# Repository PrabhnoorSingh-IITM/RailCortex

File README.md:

# 🚄 RailCortex

<p align="center">
  <a href="https://drive.google.com/file/d/1XESk1WhmcyDZzcQoyr-ekqZNMPGzPJtn/view?usp=sharing"><strong>Watch Demo Video</strong></a> | 
  <a href="https://drive.google.com/file/d/1N0aOrDR9K62Z9wJUEEKm0sZDDuzc8ooX/view?usp=sharing"><strong>View Pitch Deck (PPT)</strong></a>
</p>

RailCortex is an autonomous, dual-mode Cyber-Physical System (CPS) engineered to modernize transit operations. It replaces passive tracking with an active cognitive network, bridging the gap between **deterministic mathematical optimization**, **custom physical hardware**, and **Agentic AI**.

In its primary state, RailCortex operates as a **Level 4 Digital Twin**. Powered by a high-performance WebGL rendering engine, it visualizes spatial datasets at 60fps. Rather than relying on human dispatchers to resolve platform conflicts, the system ingests live edge telemetry and utilizes **Mixed-Integer Linear Programming (MILP)** via PuLP to deterministically reroute trains, absorbing localized delays before they cascade across the grid.

When a physical disaster strikes, RailCortex’s custom-engineered IoT edge node—equipped with an MPU6050 accelerometer, NEO-6M GPS, and environmental sensors—detects the kinetic anomaly and instantly overrides the network. The system transitions into **Emergency Response Mode**, deploying a rigid, deterministic **LangGraph Multi-Agent Swarm**.

---

## 🧭 Dual-Mode Capabilities

### 1. Normal Operations: The Digital Twin
A high-performance WebGL spatial dashboard that functions as a Level 4 digital twin of the physical railway infrastructure.
*   **Live Telemetry Ingestion:** Continuously tracks real-time train movement, velocity, and track congestion parameters via WebSockets.
*   **Mathematical Rerouting:** Utilizes Mixed-Integer Linear Programming (MILP) to autonomously calculate platform reallocations and prevent network gridlock during extreme weather anomalies or track blockages.
*   **GPU-Accelerated Rendering:** Leverages `deck.gl` to render massive spatial datasets (dynamic agents, stations, meteorological overlays) at 60fps without browser latency.

### 2. Emergency Response: The Multi-Agent Swarm
Upon detection of a catastrophic event (e.g., derailment) via the custom IoT hardware edge node, the system interrupts standard optimization protocols and deploys an autonomous LangGraph agent swarm.
*   **Zero-Latency Orchestration:** Agents autonomously calculate incident severity based on raw G-force telemetry.
*   **Spatial Discovery:** Executes Overpass QL to programmatically query OpenStreetMap (OSM) for the precise GPS bounding boxes of adjacent medical infrastructure.
*   **Heavy-Vehicle CAD Routing:** Interfaces with Mappls/Google Routes REST APIs to dispatch emergency medical services utilizing traffic-aware, heavy-vehicle optimal trajectories.

---

## 🛠️ Technology Stack
This project strictly avoids simplistic API wrapper methodologies, demonstrating comprehensive engineering execution across hardware, frontend visualization, and algorithmic routing.

### Frontend (Visualization & Interactivity)
*   **Frameworks:** React.js (Vite) + Tailwind CSS + Framer Motion.
*   **Geospatial:** `deck.gl` (WebGL2 / WebGPU spatial rendering framework) + `react-map-gl` (Mapbox GL JS base maps).
*   **State Management:** Zustand (for reactive, global dashboard state).
*   **Animations:** Anime.js (for SVG architecture flows) + Framer Motion (for spring-physics layout reveals).

### Backend (Cognitive & Routing Engine)
*   **Core:** Python 3.11 + FastAPI + WebSockets (for continuous bidirectional telemetry streaming).
*   **Mathematical Optimization:** PuLP (Python-based MILP solver for deterministic routing).
*   **Agentic Framework:** LangGraph + LangChain (Strict state-machine agent orchestration).
*   **LLMs:** OpenAI GPT-4o / GPT-4o-mini (for unstructured parsing and heuristic judgment).

### Hardware Edge Node (IoT)
*   **Microcontroller:** ESP32-WROOM-32.
*   **Sensors:** MPU6050 (Accelerometer/Gyroscope) + NEO-6M (GPS) + BME280 (Meteorological Sensor) + VL53L0X (LiDAR/Time-of-Flight).
*   **Hardware Engineering:** Custom schematics and Gerber files designed in KiCad 8.0.
*   **CAD Enclosure:** 3D-printed housing parametrically modeled in Autodesk Fusion 360.
*(Note: Hardware schematics, Gerber files, and CAD deliverables are located in the `/Hardware` directory).*

---

## 📐 Engineering Principles and Deterministic Architecture
RailCortex was engineered utilizing deterministic mathematics to ensure the safe management of physical infrastructure:
*   **Deterministic Optimization Constraints:** Train platform reallocation and collision avoidance are managed by strict Linear Algebra equations and bounds, explicitly preventing stochastic LLMs from hallucinating physical routes.
*   **Graph-Based Agent State Management:** LangGraph was selected over standard conversational frameworks (e.g., AutoGen, CrewAI) to enforce a rigid, deterministic execution loop during critical emergencies, mathematically guaranteeing fallback protocols if an external API fails.
*   **Hardware-in-the-Loop Integration:** Physical severity and infrastructure degradation models (Kinetic Energy & Weibull Degradation) are calculated directly from physical IoT sensor payloads, eliminating reliance on simulated mock data for critical triggers.

---

## ⚙️ Local Setup Instructions

### 1. Repository Configuration
Clone the repository and enter the directory:
```bash
git clone https://github.com/PrabhnoorSingh-IITM/RailCortex.git
cd RailCortex
```

### 2. Backend Configuration (FastAPI)
```bash
cd backend
python3 -m venv venv
source venv/bin/activate  # On Windows use: venv\Scripts\activate
pip install -r requirements.txt
```

Create a `.env` file within the `/backend` directory:
```env
OPENAI_API_KEY=your_openai_key
MAPPLS_API_KEY=your_routing_key
MAPBOX_ACCESS_TOKEN=your_mapbox_key
```

Initialize the ASGI server:
```bash
uvicorn app.main:app --reload --port 8000
```

### 3. Frontend Configuration (React/Vite)
In a new terminal window:
```bash
cd frontend
npm install
npm run dev
```
Navigate to `http://localhost:5173` to access the Digital Twin interface.

### 4. Hardware Node Deployment 
Navigate to `/Hardware/firmware/RailCortex.ino` and flash the compiled binary to the ESP32 via the Arduino IDE. Modify the Wi-Fi credentials and target WebSocket IP address within the source code to establish a connection with the local FastAPI instance.

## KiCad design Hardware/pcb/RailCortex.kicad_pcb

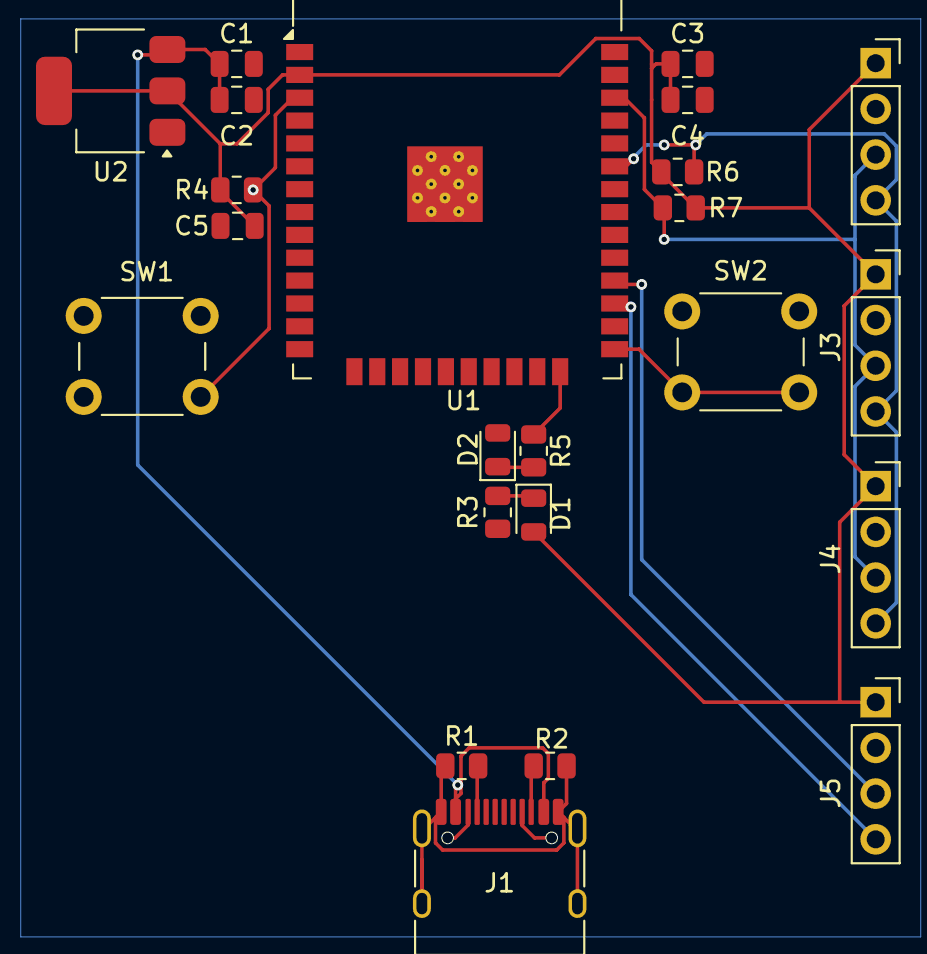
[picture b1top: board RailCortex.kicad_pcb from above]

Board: 2 copper layers, 23 parts (0 on the bottom side), 14 nets.

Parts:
C1, C3: 10 uF; C_0805_2012Metric
C2, C4: 0.1 uF; C_0805_2012Metric
C5: 1 uF; C_0805_2012Metric
D1, D2: LED; LED_0805_2012Metric
J1: USB_C_Receptacle_USB2.0_14P; USB_C_Receptacle_HRO_TYPE-C-31-M-12
J2, J3, J4, J5: Conn_Socket; PinSocket_1x04_P2.54mm_Vertical
R1, R2: 5.1 k; R_0805_2012Metric
R3, R5: 1 k; R_0805_2012Metric
R4: 10 k; R_0805_2012Metric
R6, R7: 4.7 k; R_0805_2012Metric
SW1, SW2: SW_Push; SW_PUSH_6mm
U1: ESP32-WROOM-32
U2: AMS1117-3.3; SOT-223-3_TabPin2

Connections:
+3V3: C3.1, C4.1, C5.1, D1.2 (A), J2.1, J3.1, J4.1, J5.1, R4.1, R6.1, R7.1, U1.2 (VDD), U2.2 (VO)
+5V: C1.1, C2.1, J1.A4 (VBUS), J1.A9 (VBUS), J1.B4 (VBUS), J1.B9 (VBUS), U2.3 (VI)
/GPS_RX: J5.3, U1.28 (IO17)
/GPS_TX: J5.4, U1.27 (IO16)
/SCL: J2.3, J3.3, J4.3, R7.2, U1.36 (IO22)
/SDA: J2.4, J3.4, J4.4, R6.2, U1.33 (IO21)
GND: C1.2, C2.2, C3.2, C4.2, C5.2, D2.2 (A), J1.A1 (GND), J1.A12 (GND), J1.B1 (GND), J1.B12 (GND), J1.SH (SHIELD), J2.2, J3.2, J4.2, J5.2, R1.1, R2.1, R3.1, SW1.1, SW2.2, U1.1 (GND), U1.15 (GND), U1.38 (GND), U1.39 (GND), U2.1 (GND)
unnamed: D1.1 (K), R3.2
unnamed: D2.1 (K), R5.1
unnamed: J1.A5 (CC1), R1.2
unnamed: J1.B5 (CC2), R2.2
unnamed: R4.2, SW1.2, U1.3 (EN)
unnamed: SW2.1, U1.25 (IO0)
unnamed: R5.2, U1.24 (IO2)

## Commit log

2026-06-13 Implement AI & ML for Demo
2026-06-13 Added backend implementation
2026-06-13 added frontend , dashboard
2026-06-13 finalize frontend landing page UI and align architecture details
2026-06-14 Work in progress
2026-06-14 Updated backend services and configuration
2026-06-14 Connect Frontend To Backend & Add Further Functionality
2026-06-14 Final Commit - Round 1
